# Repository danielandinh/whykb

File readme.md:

# Custom Keyboard Project

40% board w oled and knob

## Handwired Prototype
<sup><sub>not a bomb</sub></sup>

keyboard specs:
* GMK Pixel
* Gateron Milky Yellows L/F
* [3D Printed Plate](cad/plate_whole.stl)
* Durock plate mount stabs
* OLED and Knob

## PCB for sea-picro board

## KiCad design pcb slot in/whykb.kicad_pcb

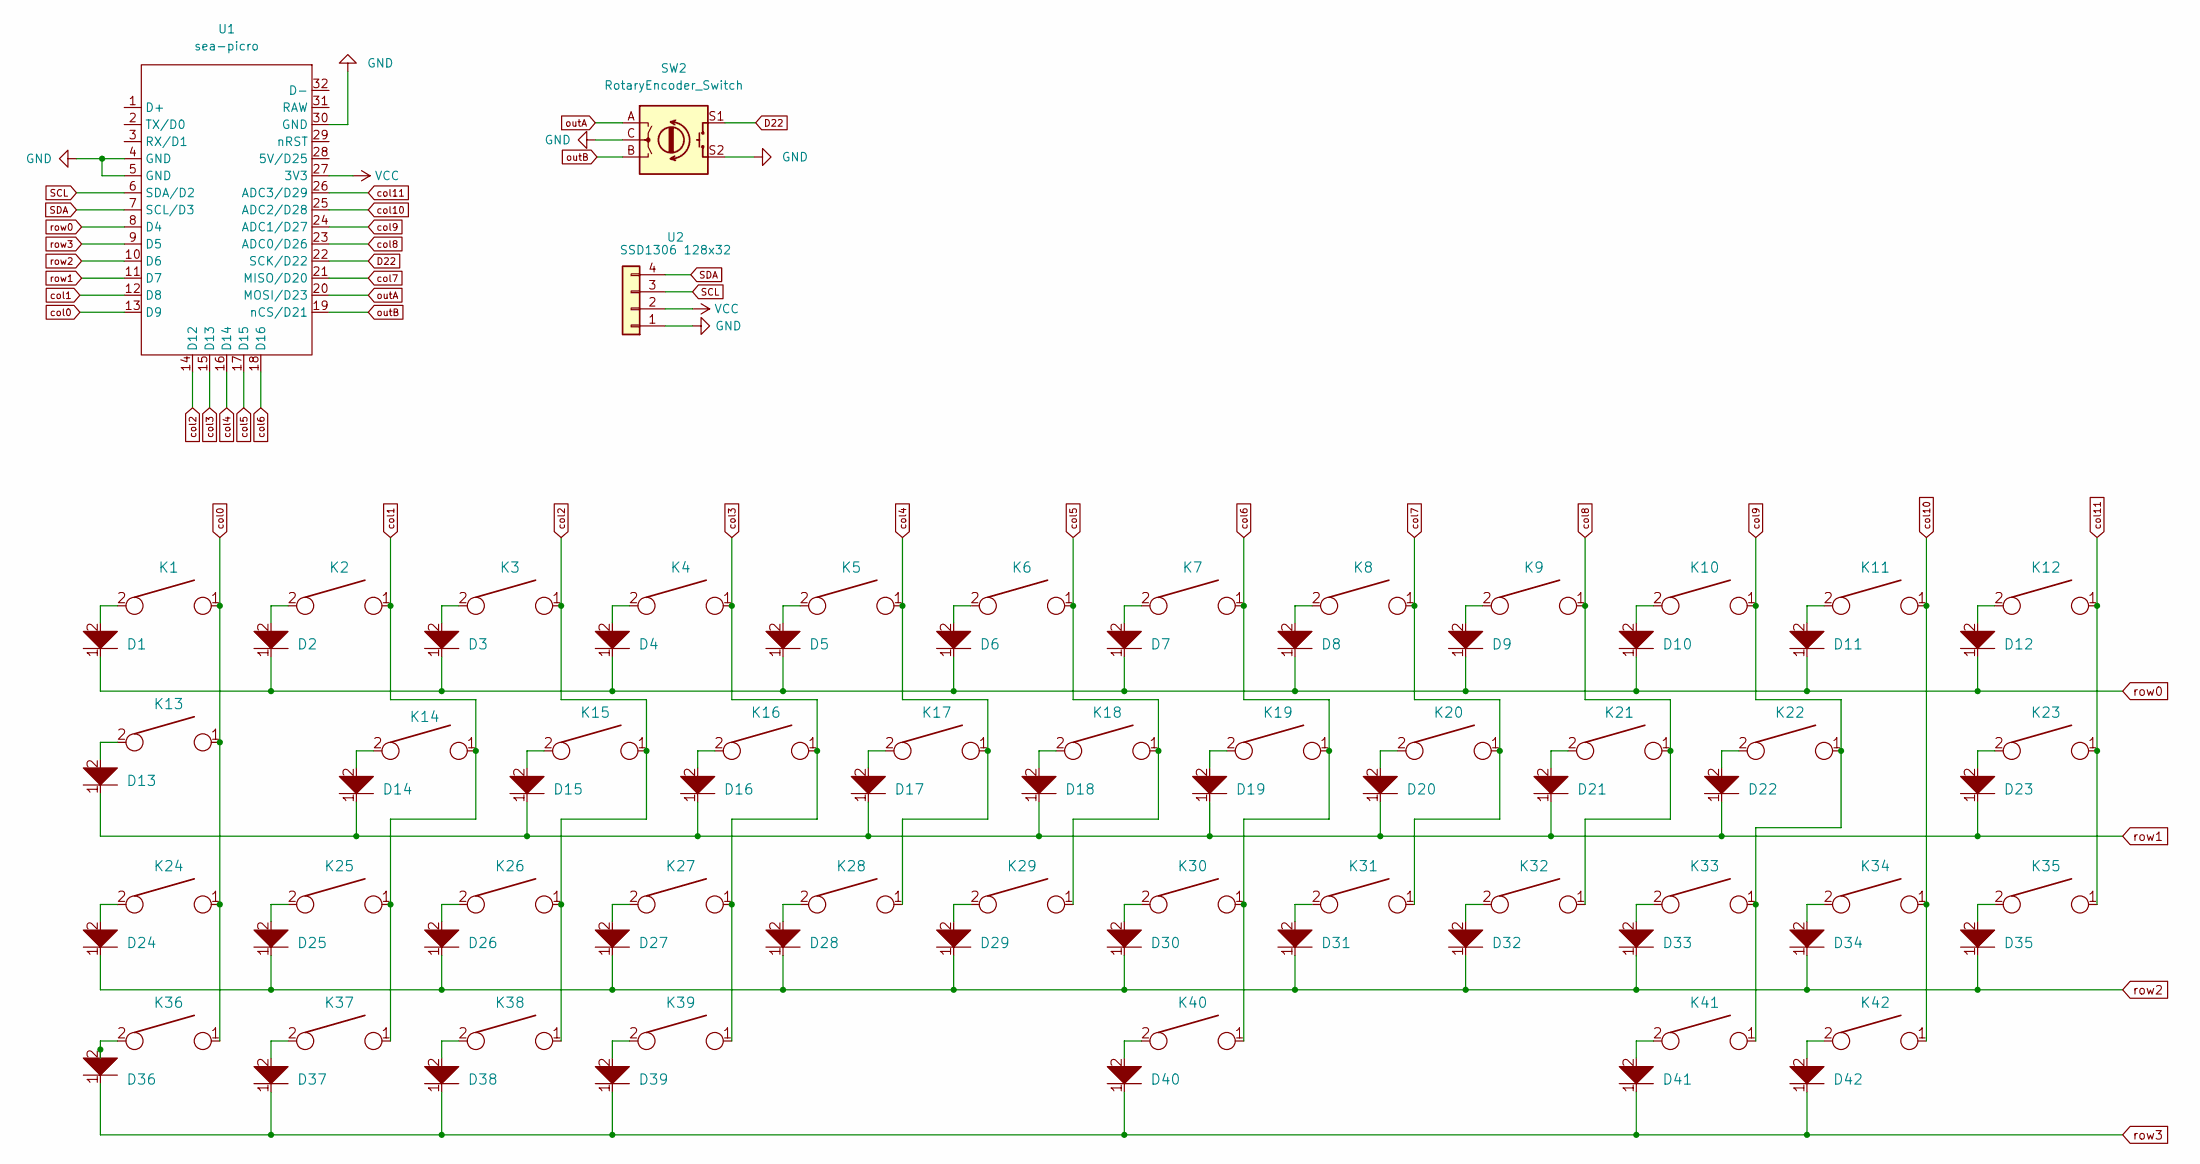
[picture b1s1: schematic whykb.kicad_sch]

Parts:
D1, D2, D3, D4, D5, D6, D7, D8, D9, D10, D11, D12, D13, D14, D15, D16, D17, D18, D19, D20, D21, D22, D23, D24, D25, D26, D27, D28, D29, D30, D31, D32, D33, D34, D35, D36, D37, D38, D39, D40, D41, D42: D; D_SOD123
K1, K12: KEYSW; MXOnly-1.5U-NoLED
K2, K3, K4, K5, K6, K7, K8, K9, K10, K11, K14, K15, K16, K17, K18, K19, K20, K21, K22, K24, K26, K27, K28, K29, K30, K31, K32, K33, K34, K36, K37, K38, K39, K42: KEYSW; MXOnly-1U-NoLED
K13: KEYSW; MXOnly-2.25U-NoLED
K23, K25: KEYSW; MXOnly-1.75U-NoLED
K35, K41: KEYSW; MXOnly-1.25U-NoLED
K40: KEYSW; MXOnly-7U-NoLED
SW2: RotaryEncoder_Switch; RotaryEncoder_Alps_EC11E-Switch_Vertical_H20mm
U1: sea-picro
U2: SSD1306 128x32; SSD1306-0.91-OLED-4pin-128x32

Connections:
D22: SW2.S1, U1.22 (SCK/D22)
GND: SW2.C, SW2.S2, U1.4 (GND), U1.5 (GND), U1.30 (GND), U2.1
unnamed: D1.2, K1.2
unnamed: D2.2, K2.2
unnamed: D3.2, K3.2
unnamed: D4.2, K4.2
unnamed: D5.2, K5.2
unnamed: D6.2, K6.2
unnamed: D7.2, K7.2
unnamed: D8.2, K8.2
unnamed: D9.2, K9.2
unnamed: D10.2, K10.2
unnamed: D11.2, K11.2
unnamed: D12.2, K12.2
unnamed: D13.2, K13.2
unnamed: D14.2, K14.2
unnamed: D15.2, K15.2
unnamed: D16.2, K16.2
unnamed: D17.2, K17.2
unnamed: D18.2, K18.2
unnamed: D19.2, K19.2
unnamed: D20.2, K20.2
unnamed: D21.2, K21.2
unnamed: D22.2, K22.2
unnamed: D23.2, K23.2
unnamed: D24.2, K24.2
unnamed: D25.2, K25.2
unnamed: D26.2, K26.2
unnamed: D27.2, K27.2
unnamed: D28.2, K28.2
unnamed: D29.2, K29.2
unnamed: D30.2, K30.2
unnamed: D31.2, K31.2
unnamed: D32.2, K32.2
unnamed: D33.2, K33.2
unnamed: D34.2, K34.2
unnamed: D35.2, K35.2
unnamed: D36.2, K36.2
unnamed: D37.2, K37.2
unnamed: D38.2, K38.2
unnamed: D39.2, K39.2
unnamed: D40.2, K40.2
unnamed: D41.2, K41.2
unnamed: D42.2, K42.2
SCL: U1.6 (SDA/D2), U2.3
SDA: U1.7 (SCL/D3), U2.4
VCC: U1.27 (3V3), U2.2
col0: K1.1, K13.1, K24.1, K36.1, U1.13 (D9)
col1: K2.1, K14.1, K25.1, K37.1, U1.12 (D8)
col2: K3.1, K15.1, K26.1, K38.1, U1.14 (D12)
col3: K4.1, K16.1, K27.1, K39.1, U1.15 (D13)
col4: K5.1, K17.1, K28.1, U1.16 (D14)
col5: K6.1, K18.1, K29.1, U1.17 (D15)
col6: K7.1, K19.1, K30.1, K40.1, U1.18 (D16)
col7: K8.1, K20.1, K31.1, U1.21 (MISO/D20)
col8: K9.1, K21.1, K32.1, U1.23 (ADC0/D26)
col9: K10.1, K22.1, K33.1, K41.1, U1.24 (ADC1/D27)
col10: K11.1, K34.1, K42.1, U1.25 (ADC2/D28)
col11: K12.1, K23.1, K35.1, U1.26 (ADC3/D29)
outA: SW2.A, U1.20 (MOSI/D23)
outB: SW2.B, U1.19 (nCS/D21)
row0: D1.1, D2.1, D3.1, D4.1, D5.1, D6.1, D7.1, D8.1, D9.1, D10.1, D11.1, D12.1, U1.8 (D4)
row1: D13.1, D14.1, D15.1, D16.1, D17.1, D18.1, D19.1, D20.1, D21.1, D22.1, D23.1, U1.11 (D7)
row2: D24.1, D25.1, D26.1, D27.1, D28.1, D29.1, D30.1, D31.1, D32.1, D33.1, D34.1, D35.1, U1.10 (D6)
row3: D36.1, D37.1, D38.1, D39.1, D40.1, D41.1, D42.1, U1.9 (D5)

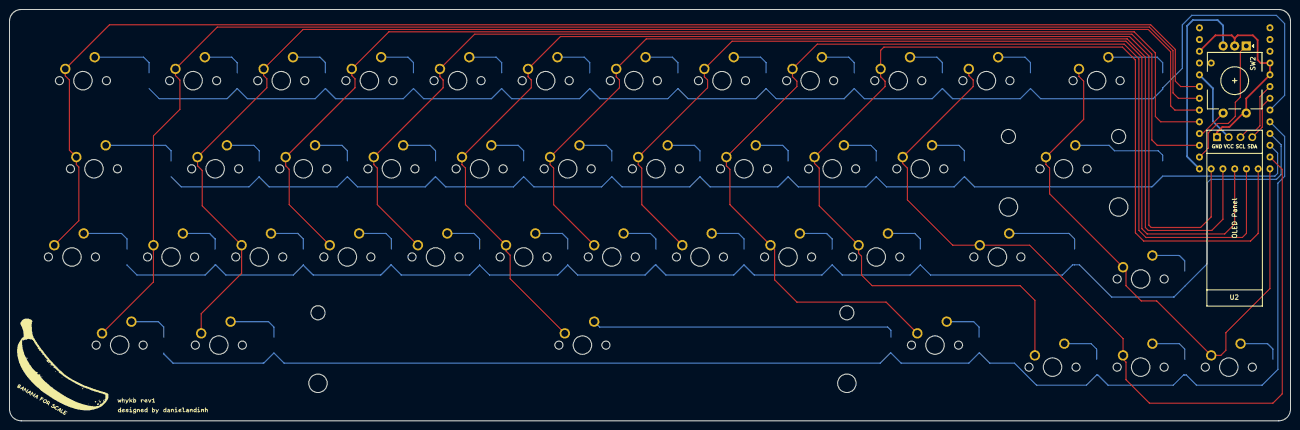
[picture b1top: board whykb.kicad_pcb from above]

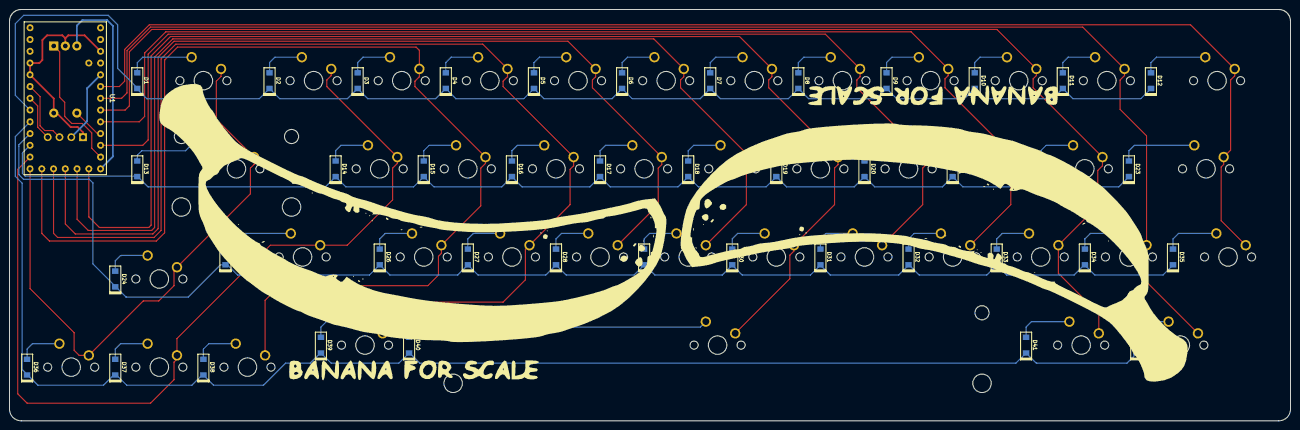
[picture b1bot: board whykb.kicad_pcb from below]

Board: 2 copper layers, 276.9 x 88.9 mm, 87 parts (43 on the bottom side), 65 nets.

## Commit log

2022-12-19 initial layout design
    added modelling/cad files for keyboard plate
2022-12-19 Create whykb_arrowcluster.json
    json file for kle (http://www.keyboard-layout-editor.com/)
2022-12-19 sorted things, added firmware
    firmware supports default qwerty layout only
2022-12-20 firmware update
    added support for rotary encoder
    added fn and num layers
2022-12-20 oled not working yet
2022-12-20 Create mcuconf.h
    no more compiling errors but nothing displaying :c
2022-12-20 changing i2c driver
    changed in config and mcuconf
2022-12-21 Update keymap.c
    removed bongo cat
2022-12-21 oled working
2022-12-21 update readme's
2023-01-27 pcb files
    - created symbol for elite c board
    - finish schematic
    - cvpcb done
2023-01-28 made sea picro footprint
2023-02-09 start pcb layout
2023-02-19 routed traces
2023-02-19 update pcb
    cleaned up traces
    added some silkscreen
    generate gerbers
2023-02-19 minor fixes
    - updated gerber setting 'subtract soldermask from silkscreen'
    - changed silkscreen
2023-02-19 added 3d models to pcb

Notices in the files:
pcb slot in/whykb.kicad_pcb:
creativecommons.org/license/by/4.0
License: CC BY 4.0
pcb slot in/whykb.kicad_sch:
creativecommons.org/licenses/by/4.0
